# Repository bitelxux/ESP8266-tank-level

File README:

2023/04/22
===================================================================================

Created branch DHT-11

2023/04/21
===================================================================================

Last kown working environment

Arduino IDE 2.1.0

Libaries:

Name                    Installed Available Location              Description                           
Adafruit_BusIO          1.14.1    -         LIBRARY_LOCATION_USER -                                     
Adafruit_GFX_Library    1.11.5    -         LIBRARY_LOCATION_USER -                                     
Adafruit_SSD1306        2.5.7     -         LIBRARY_LOCATION_USER -                                     
Adafruit_Unified_Sensor 1.1.9     -         LIBRARY_LOCATION_USER -                                     
ArduinoJson             5.13.5    6.21.2    LIBRARY_LOCATION_USER An efficient and elegant JSON library...
cnn                               -         LIBRARY_LOCATION_USER -                                     
DHT_sensor_library      1.4.4     -         LIBRARY_LOCATION_USER -                                     
ESP_DoubleResetDetector 1.3.2     -         LIBRARY_LOCATION_USER -                                     
NTPClient               3.2.1     -         LIBRARY_LOCATION_USER -                                     
WiFiManager             2.0.15-rc.1 -       LIBRARY_LOCATION_USER - 

Board: Generic ESP8266 board (3.0.2)

2022/05/13
===================================================================================

New version of https://github.com/bitelxux/levelsensor

Based in a ESP8266 reading from the sensor and uploading to a server
where very likely Grafana will show a nice chart.

It supports connection outages by storing values locally with a timestamp
and sending them once the connection is resumed.

This version will have a lot of improvements like pseudo-threads, 
smart use of EEPROM to store readings when connection to the server is not available,
WiFiManager to dynamically manage connections from any browser,
commands inyection from the server to force actions to happen in the
ESP like EEPROM reset or forget WiFis and much more !!

It's a Work in Progress !! Far from being finished !

Also the servers (tank level server and logs server) are not finished.

Link 'cnn' library to arduino's libraries directory
That 'cnn' library will be split from the main code at some point.
And it needs a proper name !

Keep syntonized if you want to see where this ends

First environment
============================================

 - Arduino IDE 1.8.15
 - Arduino AVR board 1.8.3
 - ESP8266 2.7.0

https://arduino.esp8266.com/stable/package_esp8266com_index.json
board: NodeMCU1.0 (ESP-12E Module)

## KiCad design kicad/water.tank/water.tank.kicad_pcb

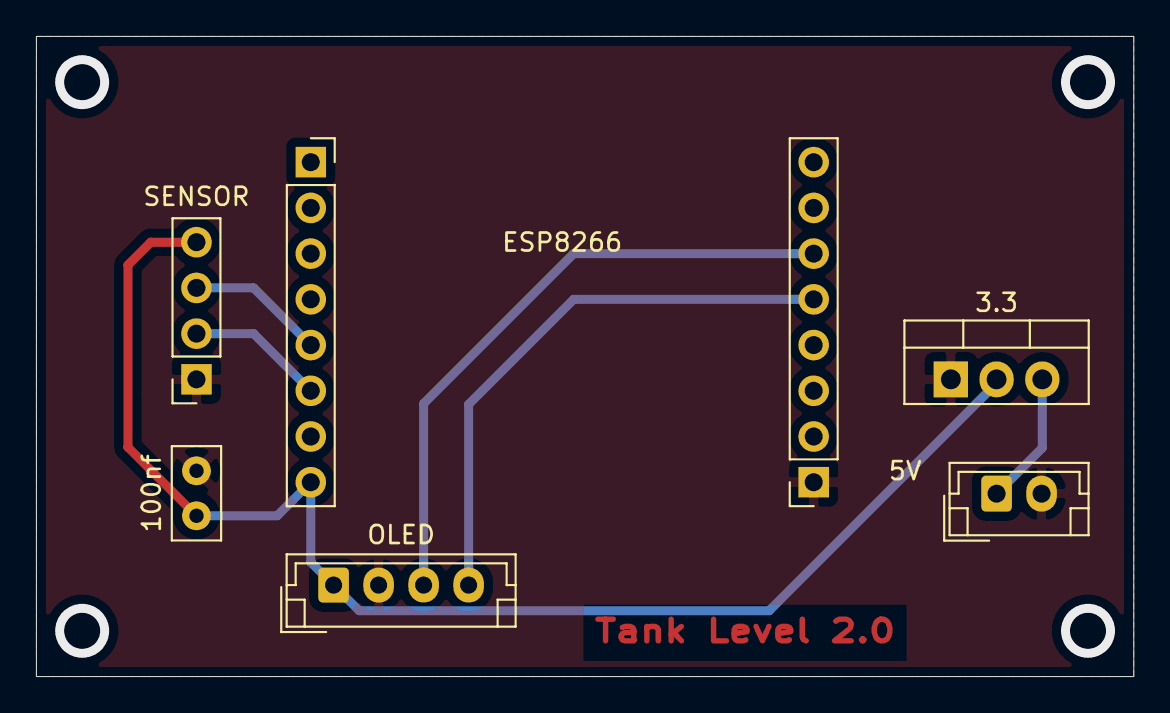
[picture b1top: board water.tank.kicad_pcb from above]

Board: 2 copper layers, 61.0 x 35.6 mm, 7 parts (0 on the bottom side), 7 nets.

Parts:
3.3: LD33V; TO-220-3_Vertical
5V: source; JST_EH_B2B-EH-A_1x02_P2.50mm_Vertical
100nf: CAP; C_Disc_D5.0mm_W2.5mm_P2.50mm
ESP8266: ESP8266; PinSocket_1x08_P2.54mm_Vertical
J1: ESP8266; PinSocket_1x08_P2.54mm_Vertical
OLED: OLED1; JST_EH_B4B-EH-A_1x04_P2.50mm_Vertical
SENSOR: r; PinSocket_1x04_P2.54mm_Vertical

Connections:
5V: 3.3.3, 5V.1
GND: 3.3.1, 5V.2, 100nf.2, ESP8266.1, OLED.2, SENSOR.1
IO04: ESP8266.5, OLED.4
IO05: ESP8266.6, OLED.3
IO12: J1.6, SENSOR.2
IO14: J1.5, SENSOR.3
VCC: 3.3.2, 100nf.1, J1.8, OLED.1, SENSOR.4

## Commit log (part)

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2022-04-17 fix Makefile
2022-04-23 WIP using a custom library
2022-04-24 timer to class method working
2022-04-24 about to support App and user timers
2022-04-24 App and user timers working
2022-04-24 the logger is now in the app
2022-04-24 connect moved to the app
2022-04-24 handleOTA moved to app
2022-04-24 update lastRun
2022-04-24 enabled rest of timers
2022-04-24 now imAlive shows IP
2022-04-24 some cleaning
2022-04-24 update doc
2022-04-24 blink led moved to app
2022-04-24 more stuff moved to the library
2022-04-24 replace pointer for object
2022-04-24 tiny log server example
2022-04-24 reorder
2022-04-24 execution permission
2022-04-24 gitignore
2022-04-27 simplify timers
2022-04-27 some tide up
2022-04-27 configure LEDs
2022-05-02 flush local data in batches
2022-05-02 chech is server is alive before flushing
2022-05-02 changed batch size to 50
2022-05-02 mobile average
2022-05-02 dealing with actual litres now
2022-05-02 purge some readings before actually reading
2022-05-05 free LEDs pins
2022-05-05 WIP. adding OLED
2022-05-06 first info on OLED
2022-05-06 re-arrange and more OLED messages
2022-05-07 more display stuff
2022-05-07 get actions from server and delete eeprom action
2022-05-08 counter slots management
2022-05-08 counters and records management in memory
2022-05-08 rename method
2022-05-08 abort flush if counter is 0
2022-05-09 flushing data
2022-05-09 flush data
2022-05-10 workaround to fix out of sync counter
2022-05-10 [7] draw tank in display
2022-05-10 wider tank
2022-05-11 [8] fixes around memory management
2022-05-11 [8] break loop on counter 0
2022-05-11 small changes
2022-05-12 [11] use WiFiManager
2022-05-12 rearrange
2022-05-13 [13] reconnect after forgetting wifis
2022-05-13 [14] get IP after connect
2022-05-13 [9] first reading
2022-05-13 use 1 byte for flag
2022-05-13 README
2022-05-13 [17] periodically sync NTP
2022-05-13 dirty fix to reach MAX_RECORDS
2022-05-13 remove some debug messages
2022-05-15 [20] support JSN mode 1
2022-05-15 [21] try several times to read a value
2022-05-15 add more resources
2022-06-04 a few unrelated things
2022-06-05 [23] start docker-compose setup
2022-06-05 [23] restart always
2022-06-05 [23] README for MySQL on ARM
2022-06-05 [23] moved to yobasystems/alpine-mariadb
2022-06-05 [23] more docker-compose
2022-06-06 [23] almost there
2022-06-06 [23] fix small typos
2022-06-06 [23] measurement
2022-06-06 [23] try/exception
2022-06-06 [23] points
2022-06-09 [24] improve times management
2022-06-09 [25] version and board id
2022-06-11 [build]
2022-06-11 [26] nanoseconds
2022-06-12 [27] wip wifimanager custom parameter for server
2022-06-12 [27] get and store server ip from wifimanager
2022-06-12 [28] fix version
2022-06-12 [na] house keeping
2022-06-12 [28][29] fix and show version
2022-06-12 [22] show name on display
2022-06-12 [26] use nanoseconds
2022-06-12 [9] flat surfaces of water
2022-06-12 [29] reset button
2022-06-26 [30][31] Rest server
2022-07-12 [33] send ID in headers
2022-07-13 [34] persistent volume for grafana
2022-07-19 [35] smarter removal of outliers
2022-07-22 [36] store readings when there is no connection
2022-07-22 [xxx] re-arrange
2022-07-22 [xxx] NTP
2022-07-23 36] reverting change as it doesn't work
2022-07-23 [37] expose influxdb
2022-07-24 [36] NTP + millis is working now
2022-07-24 [36] NTP + millis is working now (typo)
2022-07-24 [35] Not that smart removal of peaks after all
2022-07-24 [3] number of boots
2022-07-25 [3] fix boots address and add rest to get and remove warnings
2022-07-25 [xxx] nicer clear warnings endpoint
2022-07-26 [xxx] increase peak distance
2022-08-13 [38] uptime REST endpoing
2022-08-13 [38] uptime REST endpoing (fix text)
2022-08-13 [39] discard distance 0
2022-09-10 [NA] util to add annotations to grafana
2022-09-10 [NA] grafana annotations
2022-10-22 [40] add help to REST API
2022-10-29 [xxx] small changes
2022-11-01 [32] reset wifi REST API
2022-11-27 pin grafana and user
2022-12-11 [42] reset wifi REST
2022-12-11 [43] wait for router after power outage
2022-12-19 [44] reconnect
2023-04-22 [48] new arduino IDE 2.1.0
2023-04-22 [49] REST endpoint to reset boots
2023-04-23 [50] networks info
2023-04-23 [51] basic multy-target logging system
2023-04-23 [tank0.20230423.233] basic multy-target logging system
2023-04-30 [53] fix wifi reconnection
2023-04-30 [54] add basic logging capacity to the server
2023-05-01 [55] use a file to disable outlier detection
2023-05-01 [52] splash screen on boot
2023-05-02 [56] first DHT11 prototype
2023-05-02 [57] DHT11 library cut off main code
2023-05-02 [58] split tank level sensor logic from main code
2023-05-02 [59] specific draw graphic for DHT11
2023-05-02 [60] use READ_LABEL for text in display
2023-05-02 [61] initialize distance sensor
2023-05-02 [62] center wifi icon with termometer for DHT11
2023-05-02 [53] bring back changes fixing reconnection. And other minor changes
2023-05-06 [66] first version working on batteries and deep sleep
2023-05-06 [66] bring back OLED if mode is always awake
2023-05-06 [60] bring batteries branch improvementes into DHT11 branch
2023-05-09 [x] fixes around sleep mode
2023-05-23 display
2023-12-24 [wip] its broken at this point
2023-12-24 [2] dump eeprom via REST
2023-12-26 [2] improvements to dump EEPROM
2023-12-27 [67] Prevent WebPortal to start if SSID is configured
2024-04-20 change influxdb to a generic 'devices' table
2024-04-20 temporary broken method
2024-05-15 add getSum
2024-05-15 tool to delete offvalues
2024-05-15 ignore SKIP_OUTLIER_DETECTION
2024-05-15 ignore delete tool timestamps file
2024-05-15 description
2024-05-15 partialy fix outliers detection
2024-05-15 change option to -s
2024-05-15 outliers not crashing. But far from being properly implemented
2024-05-29 adjust outlier
